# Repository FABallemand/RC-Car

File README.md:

# 🏎️ Radio Controlled Car

## 🔎 Description

Building a radio-controlled car from scratch!! 

## 📚 Ressources

### 🔧 Hardware
- DroneBot Workshop: [Controlling DC Motors with the L298N H Bridge and Arduino](https://www.youtube.com/watch?v=dyjo_ggEtVU&ab_channel=DroneBotWorkshop)
- DroneBot Workshop: [Using Servo Motors with Arduino](https://www.youtube.com/watch?v=kUHmYKWwuWs&ab_channel=DroneBotWorkshop)
- DroneBot Workshop: [Bluetooth & IR Remote - Elegoo Arduino Smart Robot Car Part 2](https://www.youtube.com/watch?v=DD8sYXKe268&ab_channel=DroneBotWorkshop)
- [HC-08 Datasheet](http://www.hc01.com/downloads/HC-08A%20version%20english%20datasheet.pdf)
- DroneBot Workshop: [Using the HC-SR04 Ultrasonic Distance Sensor with Arduino - Everything you need to know!](https://www.youtube.com/watch?v=6F1B_N6LuKw&ab_channel=DroneBotWorkshop)

### 💾 Software
- MUO: [How to Manage Bluetooth Devices on Linux Using bluetoothctl](https://www.makeuseof.com/manage-bluetooth-linux-with-bluetoothctl/)
- PyPi: [PyBluez](https://pypi.org/project/PyBluez/)
- PyPi: [Bleak](https://pypi.org/project/bleak/)
- PyPi: [BluePy](https://pypi.org/project/bluepy/)
- [How to send data between PC and Arduino using Bluetooth LE](https://ladvien.com/python-serial-terminal-with-arduino-and-bleak/)
- DonovanStudio: [HOW TO: Bluetooth Arduino connecting to Python on desktop](https://www.youtube.com/watch?v=3tcn496oxnk&ab_channel=DonovanStudio)
- [How to identify which OS Python is running on?](https://stackoverflow.com/questions/1854/how-to-identify-which-os-python-is-running-on)
- Albert Huang: [An Introduction to Bluetooth Programming](https://people.csail.mit.edu/albert/bluez-intro/index.html) (Python or C)
- Wavecake: [Reading your phone's battery level over Bluetooth BLE with Python Bleak](https://getwavecake.com/blog/reading-your-phones-battery-level-over-bluetooth-ble-with-python-bleak/)

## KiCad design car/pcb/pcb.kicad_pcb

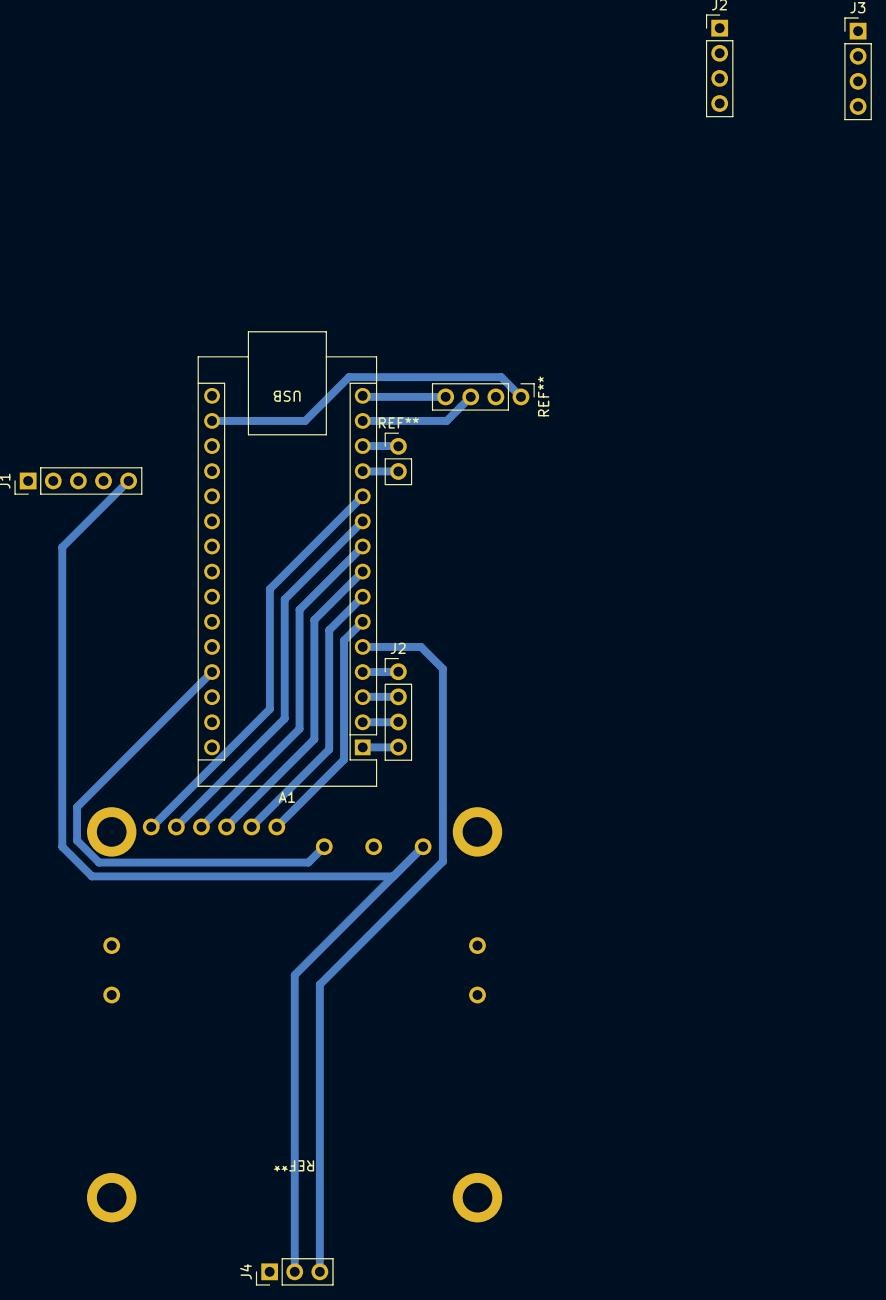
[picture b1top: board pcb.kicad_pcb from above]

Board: 2 copper layers, 6 parts (0 on the bottom side), 3 nets.

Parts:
A1: Arduino_Nano_v3.x; Arduino_Nano
J1: Conn_01x05; PinHeader_1x05_P2.54mm_Vertical
J2, J2#2, J3: Conn_01x04; PinHeader_1x04_P2.54mm_Vertical
J4: Conn_01x03; PinHeader_1x03_P2.54mm_Vertical

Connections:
GNDREF: A1.4 (GND), A1.29 (GND), J1.1, J2#2.1, J4.1
MOTORS_5V: J1.5, J4.2
SERVO: A1.5 (D2), J4.3

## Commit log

2023-01-13 Testing motors
2023-02-12 Repository organisation
2023-04-06 Working bluetooth controler
2023-04-07 First working car program
2023-04-10 Sonar tests
2023-04-11 Car program
